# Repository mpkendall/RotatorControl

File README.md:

# Controller for the STARS Rotator
## For use with the Yaesu G-5500DC rotator with custom PCB

## Development
```mv config.h.example config.h```

Fill in your configuration (notably WiFi settings).

Upload code through Arduino to the ESP-32!

*README is a work-in-progress.*
*Licensed under MIT license*

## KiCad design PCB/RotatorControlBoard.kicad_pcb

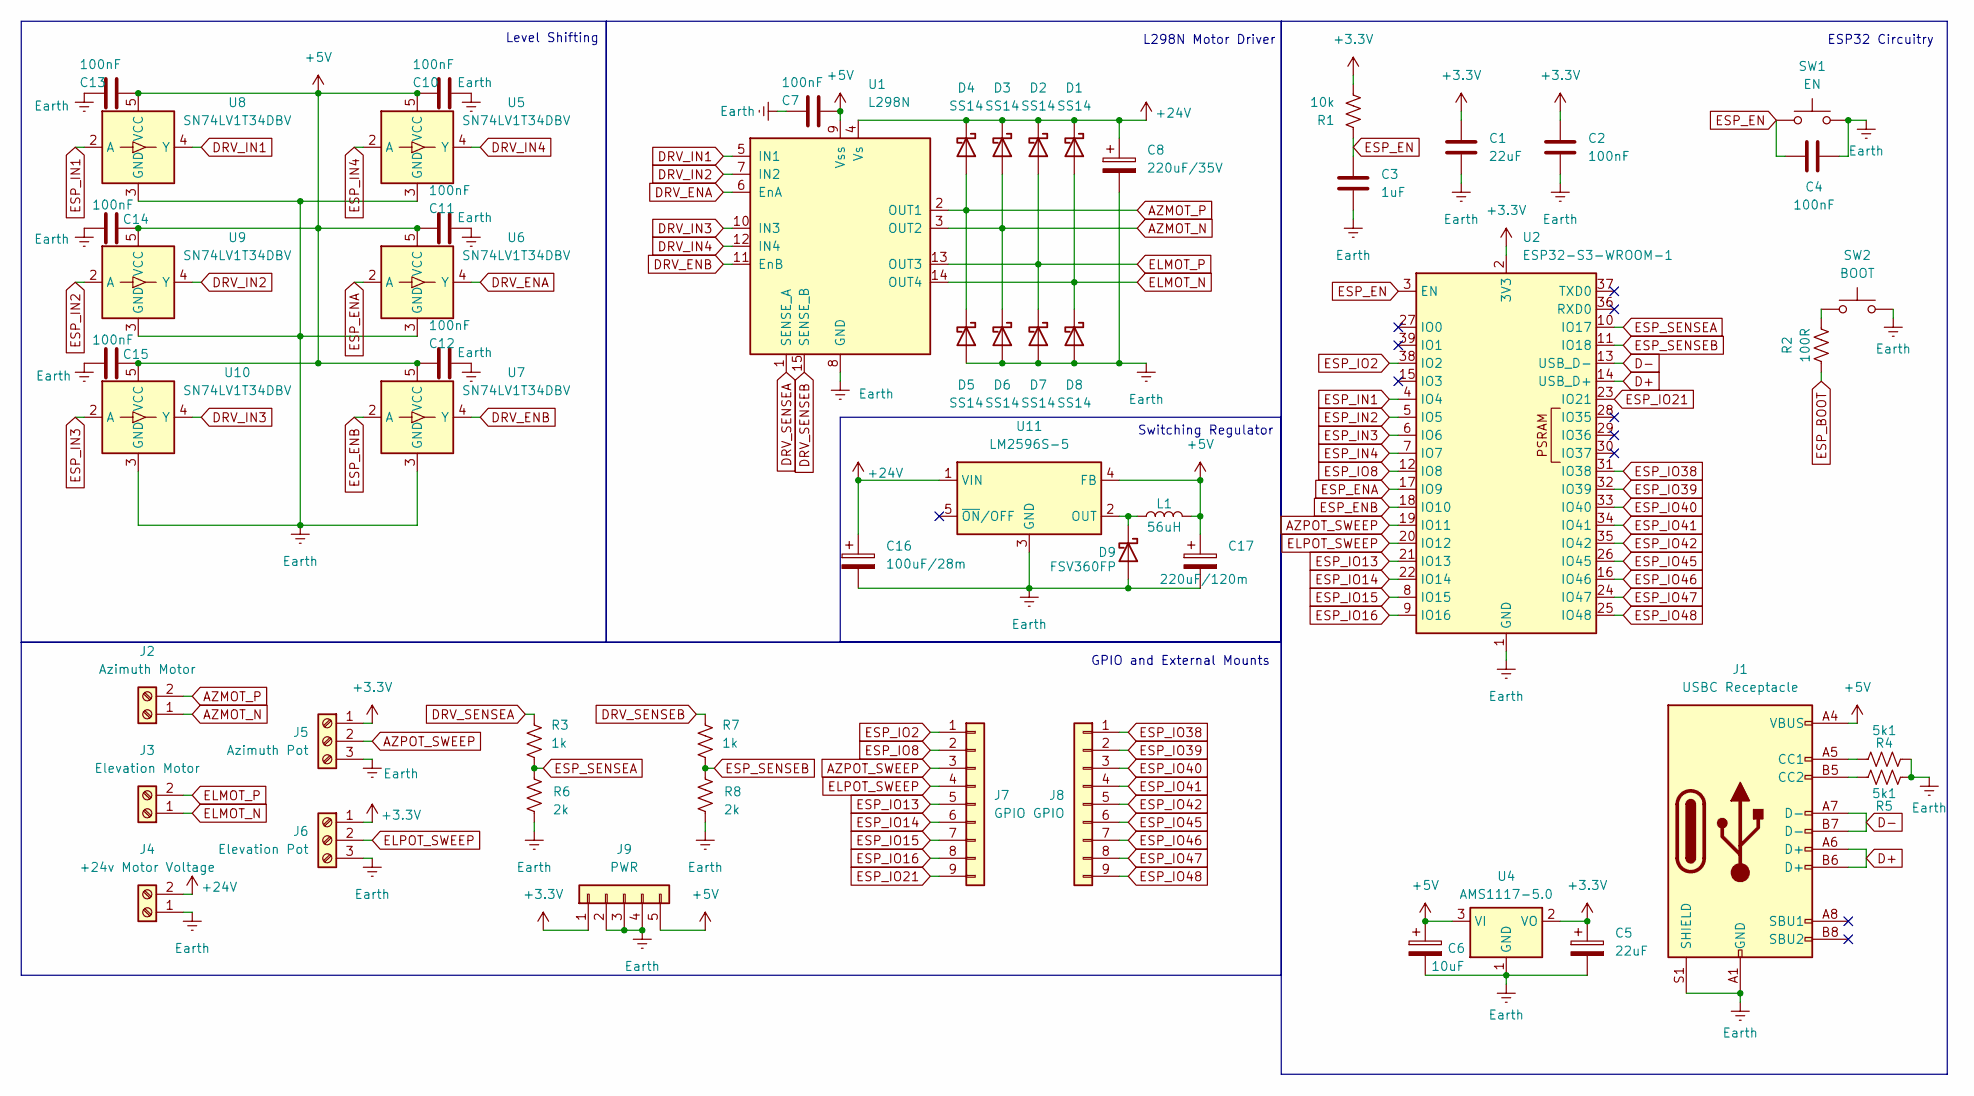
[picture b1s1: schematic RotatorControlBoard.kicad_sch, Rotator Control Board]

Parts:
C1, C5: 22uF; C_0805_2012Metric
C2, C4, C7, C10, C11, C12, C13, C14, C15: 100nF; C_0805_2012Metric
C3: 1uF; C_0805_2012Metric
C6: 10uF; C_0805_2012Metric
C8: 220uF/35V; CAP_EEE1VA221UP
C16: 100uF/28m; PCAP_EEHZ_G_PAN
C17: 220uF/120m; U2-P_NCH
D1, D2, D3, D4, D5, D6, D7, D8: SS14; D_SMA
D9: FSV360FP; B360A-13-F_DIO
J1: USBC Receptacle; USB_C_Receptacle_GCT_USB4105-xx-A_16P_TopMnt_Horizontal
J2: Azimuth Motor; TerminalBlock_MaiXu_MX126-5.0-02P_1x02_P5.00mm
J3: Elevation Motor; TerminalBlock_MaiXu_MX126-5.0-02P_1x02_P5.00mm
J4: +24v Motor Voltage; TerminalBlock_MaiXu_MX126-5.0-02P_1x02_P5.00mm
J5: Azimuth Pot; TerminalBlock_MaiXu_MX126-5.0-03P_1x03_P5.00mm
J6: Elevation Pot; TerminalBlock_MaiXu_MX126-5.0-03P_1x03_P5.00mm
J7, J8: GPIO; PinSocket_1x09_P2.54mm_Vertical
J9: PWR; PinHeader_1x05_P2.54mm_Vertical
L1: 56uH; IND_IHLP-6767GZ_VIS
R1: 10k; R_0805_2012Metric
R2: 100R; R_0805_2012Metric
R3, R7: 1k; R_0805_2012Metric
R4, R5: 5k1; R_0805_2012Metric
R6, R8: 2k; R_0805_2012Metric
SW1: EN; SW_PUSH_6mm
SW2: BOOT; SW_PUSH_6mm
U1: L298N; TO-220-15_P2.54x2.54mm_StaggerOdd_Lead4.58mm_Vertical
U2: ESP32-S3-WROOM-1
U4: AMS1117-5.0; SOT-223-3_TabPin2
U5, U6, U7, U8, U9, U10: SN74LV1T34DBV; SOT-23-5
U11: LM2596S-5; TO-263-5_TabPin3

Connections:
+3.3V: C1.1, C2.1, C5.1, J5.1, J6.1, J9.1, R1.2, U2.2 (3V3), U4.2 (VO)
+5V: C6.1, C7.1, C10.2, C11.2, C12.2, C13.1, C14.1, C15.1, C17.1, J1.A4 (VBUS), J1.A9 (VBUS), J1.B4 (VBUS), J1.B9 (VBUS), J9.5, L1.2, U1.9 (Vss), U4.3 (VI), U5.5 (VCC), U6.5 (VCC), U7.5 (VCC), U8.5 (VCC), U9.5 (VCC), U10.5 (VCC), U11.4 (FB)
+24V: C8.1, C16.1, D1.1 (K), D2.1 (K), D3.1 (K), D4.1 (K), J4.2, U1.4 (Vs), U11.1 (VIN)
AZMOT_N: D3.2 (A), D6.1 (K), J2.1, U1.3 (OUT2)
AZMOT_P: D4.2 (A), D5.1 (K), J2.2, U1.2 (OUT1)
AZPOT_SWEEP: J5.2, J7.3, U2.19 (IO11)
D+: J1.A6 (D+), J1.B6 (D+), U2.14 (USB_D+)
D-: J1.A7 (D-), J1.B7 (D-), U2.13 (USB_D-)
DRV_ENA: U1.6 (EnA), U6.4 (Y)
DRV_ENB: U1.11 (EnB), U7.4 (Y)
DRV_IN1: U1.5 (IN1), U8.4 (Y)
DRV_IN2: U1.7 (IN2), U9.4 (Y)
DRV_IN3: U1.10 (IN3), U10.4 (Y)
DRV_IN4: U1.12 (IN4), U5.4 (Y)
DRV_SENSEA: R3.1, U1.1 (SENSE_A)
DRV_SENSEB: R7.1, U1.15 (SENSE_B)
ELMOT_N: D1.2 (A), D8.1 (K), J3.1, U1.14 (OUT4)
ELMOT_P: D2.2 (A), D7.1 (K), J3.2, U1.13 (OUT3)
ELPOT_SWEEP: J6.2, J7.4, U2.20 (IO12)
ESP_BOOT: R2.2
ESP_EN: C3.1, C4.1, R1.1, SW1.1, U2.3 (EN)
ESP_ENA: U2.17 (IO9), U6.2 (A)
ESP_ENB: U2.18 (IO10), U7.2 (A)
ESP_IN1: U2.4 (IO4), U8.2 (A)
ESP_IN2: U2.5 (IO5), U9.2 (A)
ESP_IN3: U2.6 (IO6), U10.2 (A)
ESP_IN4: U2.7 (IO7), U5.2 (A)
ESP_IO2: J7.1, U2.38 (IO2)
ESP_IO8: J7.2, U2.12 (IO8)
ESP_IO13: J7.5, U2.21 (IO13)
ESP_IO14: J7.6, U2.22 (IO14)
ESP_IO15: J7.7, U2.8 (IO15)
ESP_IO16: J7.8, U2.9 (IO16)
ESP_IO21: J7.9, U2.23 (IO21)
ESP_IO38: J8.1, U2.31 (IO38)
ESP_IO39: J8.2, U2.32 (IO39)
ESP_IO40: J8.3, U2.33 (IO40)
ESP_IO41: J8.4, U2.34 (IO41)
ESP_IO42: J8.5, U2.35 (IO42)
ESP_IO45: J8.6, U2.26 (IO45)
ESP_IO46: J8.7, U2.16 (IO46)
ESP_IO47: J8.8, U2.24 (IO47)
ESP_IO48: J8.9, U2.25 (IO48)
ESP_SENSEA: R3.2, R6.1, U2.10 (IO17)
ESP_SENSEB: R7.2, R8.1, U2.11 (IO18)
Earth: C1.2, C2.2, C3.2, C4.2, C5.2, C6.2, C7.2, C8.2, C10.1, C11.1, C12.1, C13.2, C14.2, C15.2, C16.2, C17.2, D5.2 (A), D6.2 (A), D7.2 (A), D8.2 (A), D9.2 (A), J1.A1 (GND), J1.A12 (GND), J1.B1 (GND), J1.B12 (GND), J1.S1 (SHIELD), J4.1, J5.3, J6.3, J9.2, J9.3, J9.4, R4.1, R5.1, R6.2, R8.2, SW1.2, SW2.2, U1.8 (GND), U2.1 (GND), U2.40 (GND), U2.41 (GND), U4.1 (GND), U5.3 (GND), U6.3 (GND), U7.3 (GND), U8.3 (GND), U9.3 (GND), U10.3 (GND), U11.3 (GND)
unnamed: D9.1 (K), L1.1, U11.2 (OUT)
unnamed: J1.A5 (CC1), R4.2
unnamed: J1.B5 (CC2), R5.2
unnamed: R2.1, SW2.1

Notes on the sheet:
L298N Motor Driver
Switching Regulator
Level Shifting
ESP32 Circuitry
GPIO and External Mounts

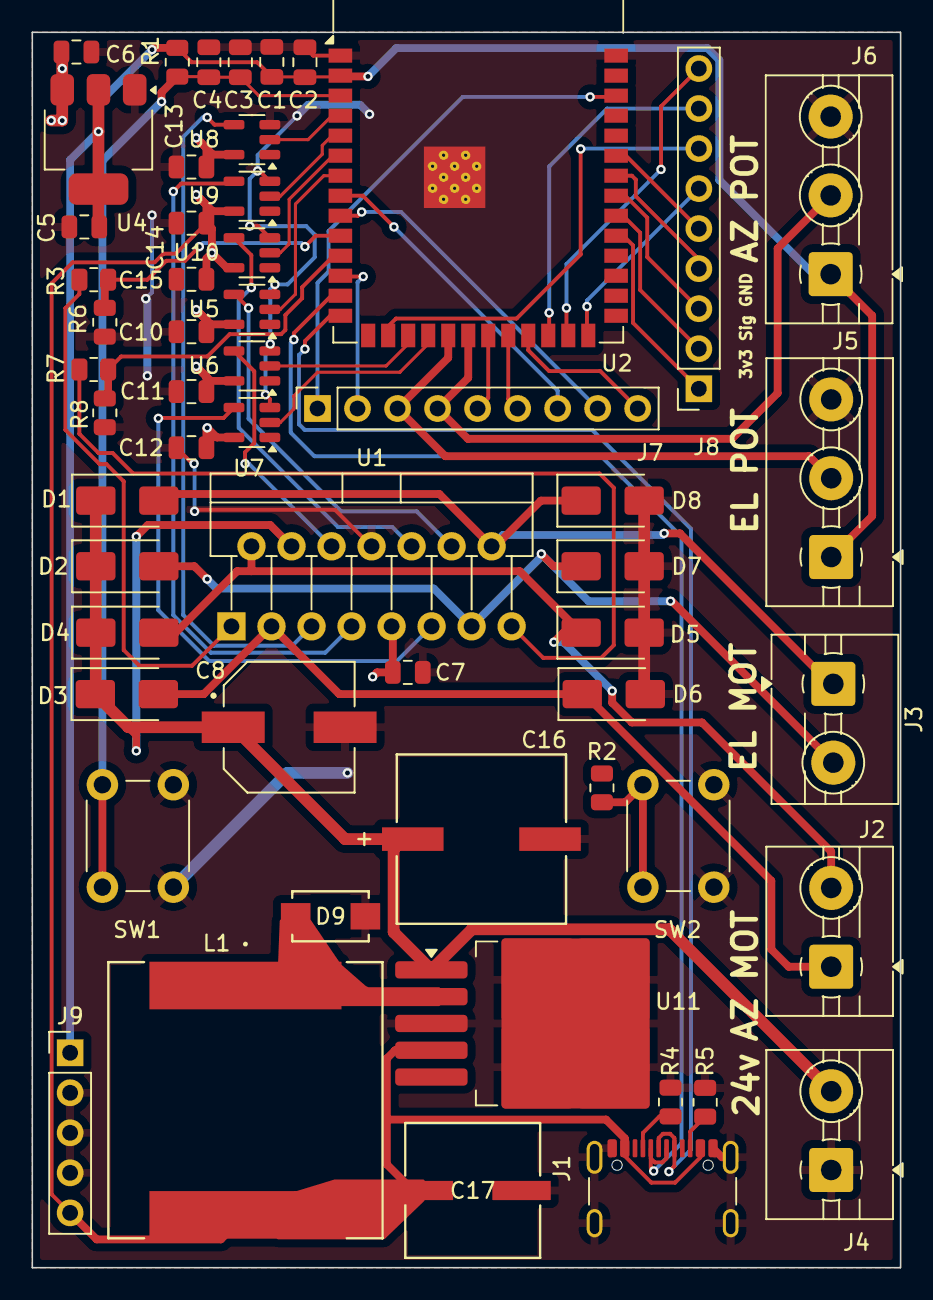
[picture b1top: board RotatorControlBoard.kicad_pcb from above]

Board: 2 copper layers, 55.1 x 78.4 mm, 55 parts (0 on the bottom side), 49 nets.

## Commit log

2025-09-13 test on real hardware
2025-09-14 calibrated el
2025-11-01 Refactor motor control limits and add calibration endpoints
2025-11-05 alpha: slew rate control
